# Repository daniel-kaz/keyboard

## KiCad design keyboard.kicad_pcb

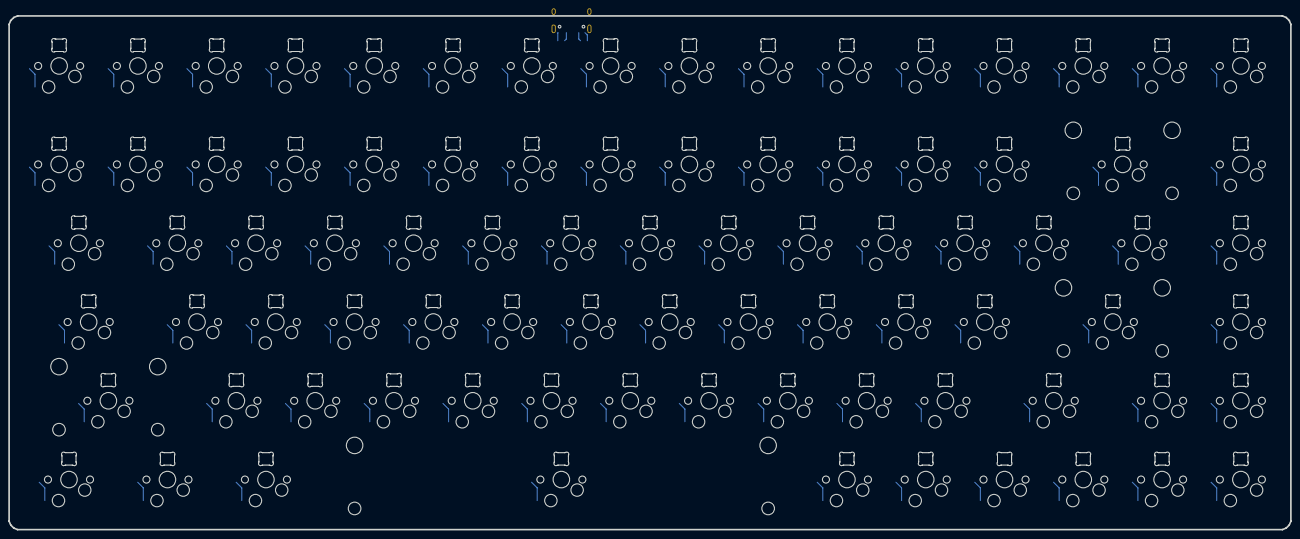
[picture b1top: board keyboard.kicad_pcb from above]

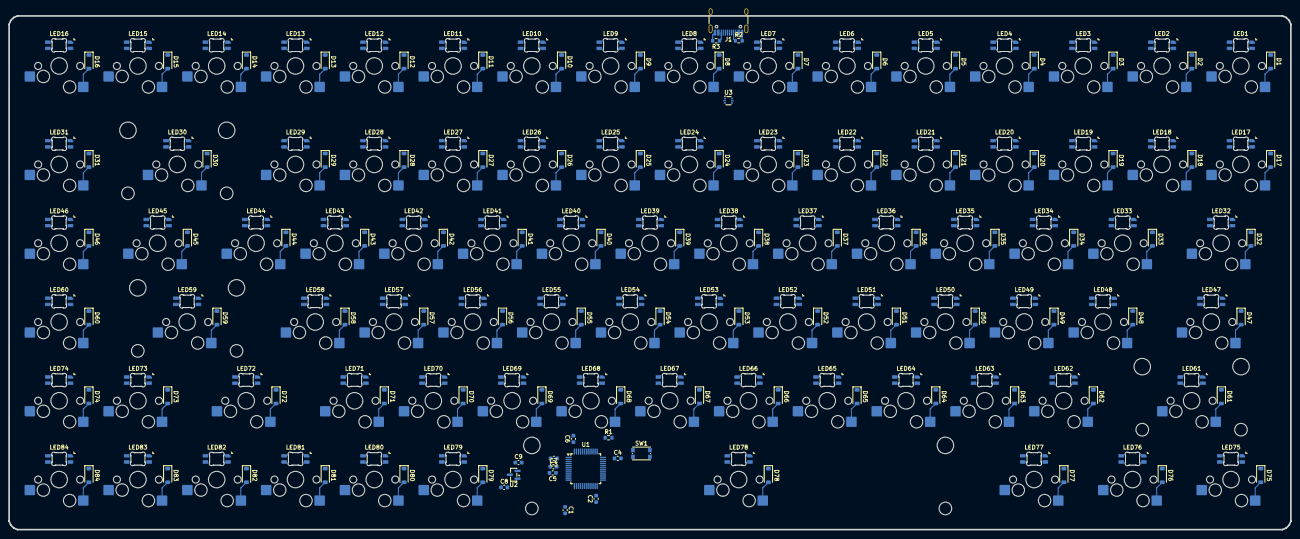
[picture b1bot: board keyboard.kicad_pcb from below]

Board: 2 copper layers, 309.9 x 124.2 mm, 279 parts (269 on the bottom side), 201 nets.

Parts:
C1: 4.7u; C_0603_1608Metric
C2, C3, C4, C5, C7: 100n; C_0603_1608Metric
C6: 10n; C_0603_1608Metric
C8, C9: 1u; C_0603_1608Metric
D1, D2, D3, D4, D5, D6, D7, D8, D9, D10, D11, D12, D13, D14, D15, D16, D17, D18, D19, D20, D21, D22, D23, D24, D25, D26, D27, D28, D29, D30, D31, D32, D33, D34, D35, D36, D37, D38, D39, D40, D41, D42, D43, D44, D45, D46, D47, D48, D49, D50, D51, D52, D53, D54, D55, D56, D57, D58, D59, D60, D61, D62, D63, D64, D65, D66, D67, D68, D69, D70, D71, D72, D73, D74, D75, D76, D77, D78, D79, D80, D81, D82, D83, D84: D; D_SOD-123
H1, H2, H3, H4, H5, H6, H7, H8, H9, H10: MountingHole; MountingHole_2.2mm_M2
J1: USB_C_Receptacle_USB2.0_14P; USB_C_Receptacle_HRO_TYPE-C-31-M-12
LED1, LED2, LED3, LED4, LED5, LED6, LED7, LED8, LED9, LED10, LED11, LED12, LED13, LED14, LED15, LED16, LED17, LED18, LED19, LED20, LED21, LED22, LED23, LED24, LED25, LED26, LED27, LED28, LED29, LED30, LED31, LED32, LED33, LED34, LED35, LED36, LED37, LED38, LED39, LED40, LED41, LED42, LED43, LED44, LED45, LED46, LED47, LED48, LED49, LED50, LED51, LED52, LED53, LED54, LED55, LED56, LED57, LED58, LED59, LED60, LED61, LED62, LED63, LED64, LED65, LED66, LED67, LED68, LED69, LED70, LED71, LED72, LED73, LED74, LED75, LED76, LED77, LED78, LED79, LED80, LED81, LED82, LED83, LED84: SK6812MINI-E; LED_6028R
R1: 10k; R_0603_1608Metric
R2, R3: 5.1k; R_0603_1608Metric
S1: ESC; MX-Hotswap-1U
S2: F1; MX-Hotswap-1U
S3: F2; MX-Hotswap-1U
S4: F3; MX-Hotswap-1U
S5: F4; MX-Hotswap-1U
S6: F5; MX-Hotswap-1U
S7: F6; MX-Hotswap-1U
S8: F7; MX-Hotswap-1U
S9: F8; MX-Hotswap-1U
S10: F9; MX-Hotswap-1U
S11: F10; MX-Hotswap-1U
S12: F11; MX-Hotswap-1U
S13: F12; MX-Hotswap-1U
S14: F13; MX-Hotswap-1U
S15: F14; MX-Hotswap-1U
S16: Magic; MX-Hotswap-1U
S17: GRV; MX-Hotswap-1U
S18: #1; MX-Hotswap-1U
S19: #2; MX-Hotswap-1U
S20: #3; MX-Hotswap-1U
S21: #4; MX-Hotswap-1U
S22: #5; MX-Hotswap-1U
S23: #6; MX-Hotswap-1U
S24: #7; MX-Hotswap-1U
S25: #8; MX-Hotswap-1U
S26: #9; MX-Hotswap-1U
S27: #0; MX-Hotswap-1U
S28: -; MX-Hotswap-1U
S29: =; MX-Hotswap-1U
S30: Backspace; MX-Hotswap-2U
S31: pgup; MX-Hotswap-1U
S32: Tab; MX-Hotswap-1.5U
S33: Q; MX-Hotswap-1U
S34: W; MX-Hotswap-1U
S35: E; MX-Hotswap-1U
S36: R; MX-Hotswap-1U
S37: T; MX-Hotswap-1U
S38: Y; MX-Hotswap-1U
S39: U; MX-Hotswap-1U
S40: I; MX-Hotswap-1U
S41: O; MX-Hotswap-1U
S42: P; MX-Hotswap-1U
S43: {; MX-Hotswap-1U
S44: }; MX-Hotswap-1U
S45: |; MX-Hotswap-1.5U
S46: pgdn; MX-Hotswap-1U
S47: CAPS; MX-Hotswap-1.75U
S48: A; MX-Hotswap-1U
S49: S; MX-Hotswap-1U
S50: D; MX-Hotswap-1U
S51: F; MX-Hotswap-1U
S52: G; MX-Hotswap-1U
S53: H; MX-Hotswap-1U
S54: J; MX-Hotswap-1U
S55: K; MX-Hotswap-1U
S56: L; MX-Hotswap-1U
S57: :; MX-Hotswap-1U
S58: "; MX-Hotswap-1U
S59: Enter; MX-Hotswap-2.25U
S60: Home; MX-Hotswap-1U
S61: LSHIFT; MX-Hotswap-2.25U
S62: Z; MX-Hotswap-1U
S63: X; MX-Hotswap-1U
S64: C; MX-Hotswap-1U
S65: V; MX-Hotswap-1U
S66: B; MX-Hotswap-1U
S67: N; MX-Hotswap-1U
S68: M; MX-Hotswap-1U
S69: <; MX-Hotswap-1U
S70: >; MX-Hotswap-1U
S71: ?; MX-Hotswap-1U
S72: RSHIFT; MX-Hotswap-1.75U
S73: UP; MX-Hotswap-1U
S74: End; MX-Hotswap-1U
S75: LCtrl; MX-Hotswap-1.25U
S76: LWin; MX-Hotswap-1.25U
S77: Alt; MX-Hotswap-1.25U
S78: Space; MX-Hotswap-6.25U
S79: RWin; MX-Hotswap-1U
S80: Fn; MX-Hotswap-1U
S81: RCtrl; MX-Hotswap-1U
S82: LEFT; MX-Hotswap-1U
S83: DOWN; MX-Hotswap-1U
S84: RIGHT; MX-Hotswap-1U
SW1: SW_Push; SW_Push_1P1T_NO_CK_KMR2
U1: STM32F072C8Tx; LQFP-48_7x7mm_P0.5mm
U2: MCP1700x-330xxTT; SOT-23
U3: USBLC6-2P6; SOT-666

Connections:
+3V3: C1.1, C2.1, C3.1, C4.1, C5.1, C6.1, C9.1, SW1.1, U1.1 (VBAT), U1.9 (VDDA), U1.24 (VDD), U1.36 (VDDIO2), U1.48 (VDD), U2.2 (VO)
+5V: C8.1, J1.A4 (VBUS), J1.A9 (VBUS), J1.B4 (VBUS), J1.B9 (VBUS), LED1.1 (VDD), LED2.1 (VDD), LED3.1 (VDD), LED4.1 (VDD), LED5.1 (VDD), LED6.1 (VDD), LED7.1 (VDD), LED8.1 (VDD), LED9.1 (VDD), LED10.1 (VDD), LED11.1 (VDD), LED12.1 (VDD), LED13.1 (VDD), LED14.1 (VDD), LED15.1 (VDD), LED16.1 (VDD), LED17.1 (VDD), LED18.1 (VDD), LED19.1 (VDD), LED20.1 (VDD), LED21.1 (VDD), LED22.1 (VDD), LED23.1 (VDD), LED24.1 (VDD), LED25.1 (VDD), LED26.1 (VDD), LED27.1 (VDD), LED28.1 (VDD), LED29.1 (VDD), LED30.1 (VDD), LED31.1 (VDD), LED32.1 (VDD), LED33.1 (VDD), LED34.1 (VDD), LED35.1 (VDD), LED36.1 (VDD), LED37.1 (VDD), LED38.1 (VDD), LED39.1 (VDD), LED40.1 (VDD), LED41.1 (VDD), LED42.1 (VDD), LED43.1 (VDD), LED44.1 (VDD), LED45.1 (VDD), LED46.1 (VDD), LED47.1 (VDD), LED48.1 (VDD), LED49.1 (VDD), LED50.1 (VDD), LED51.1 (VDD), LED52.1 (VDD), LED53.1 (VDD), LED54.1 (VDD), LED55.1 (VDD), LED56.1 (VDD), LED57.1 (VDD), LED58.1 (VDD), LED59.1 (VDD), LED60.1 (VDD), LED61.1 (VDD), LED62.1 (VDD), LED63.1 (VDD), LED64.1 (VDD), LED65.1 (VDD), LED66.1 (VDD), LED67.1 (VDD), LED68.1 (VDD), LED69.1 (VDD), LED70.1 (VDD), LED71.1 (VDD), LED72.1 (VDD), LED73.1 (VDD), LED74.1 (VDD), LED75.1 (VDD), LED76.1 (VDD), LED77.1 (VDD), LED78.1 (VDD), LED79.1 (VDD), LED80.1 (VDD), LED81.1 (VDD), LED82.1 (VDD), LED83.1 (VDD), LED84.1 (VDD), U2.3 (VI), U3.5 (VBUS)
/ARGB_DIN: LED1.3 (DIN), U1.34 (PA13)
/BOOT0: R1.1, SW1.2, U1.44 (BOOT0)
/MCU_DN: U1.32 (PA11), U3.3 (I/O2)
/MCU_DP: U1.33 (PA12), U3.1 (I/O1)
/USB_DN: J1.A6 (D+), J1.B6 (D+), U3.4 (I/O2)
/USB_DP: J1.A7 (D-), J1.B7 (D-), U3.6 (I/O1)
Col 0: S1.1, S17.1, S32.1, S47.1, S61.1, S75.1, U1.28 (PB15)
Col 1: S2.1, S18.1, S33.1, S48.1, S62.1, S76.1, U1.27 (PB14)
Col 2: S3.1, S19.1, S34.1, S49.1, S63.1, S77.1, U1.26 (PB13)
Col 3: S4.1, S20.1, S35.1, S50.1, S64.1, U1.25 (PB12)
Col 4: S5.1, S21.1, S36.1, S51.1, S65.1, U1.22 (PB11)
Col 5: S6.1, S22.1, S37.1, S52.1, S66.1, S78.1, U1.21 (PB10)
Col 6: S7.1, S23.1, S38.1, S53.1, S67.1, U1.46 (PB9)
Col 7: S8.1, S24.1, S39.1, S54.1, S68.1, U1.45 (PB8)
Col 8: S9.1, S25.1, S40.1, S55.1, S69.1, U1.43 (PB7)
Col 9: S10.1, S26.1, S41.1, S56.1, S70.1, S79.1, U1.42 (PB6)
Col 10: S11.1, S27.1, S42.1, S57.1, S71.1, S80.1, U1.41 (PB5)
Col 11: S12.1, S28.1, S43.1, S58.1, S81.1, U1.40 (PB4)
Col 12: S13.1, S29.1, S44.1, S72.1, S82.1, U1.39 (PB3)
Col 13: S14.1, S30.1, S45.1, S59.1, S73.1, S83.1, U1.20 (PB2)
Col 14: S15.1, S31.1, S46.1, S60.1, S74.1, S84.1, U1.19 (PB1), U1.30 (PA9)
Col 15: S16.1, U1.29 (PA8)
GND: C1.2, C2.2, C3.2, C4.2, C5.2, C6.2, C7.1, C8.2, C9.2, J1.A1 (GND), J1.A12 (GND), J1.B1 (GND), J1.B12 (GND), J1.S1 (SHIELD), LED1.4 (VSS), LED2.4 (VSS), LED3.4 (VSS), LED4.4 (VSS), LED5.4 (VSS), LED6.4 (VSS), LED7.4 (VSS), LED8.4 (VSS), LED9.4 (VSS), LED10.4 (VSS), LED11.4 (VSS), LED12.4 (VSS), LED13.4 (VSS), LED14.4 (VSS), LED15.4 (VSS), LED16.4 (VSS), LED17.4 (VSS), LED18.4 (VSS), LED19.4 (VSS), LED20.4 (VSS), LED21.4 (VSS), LED22.4 (VSS), LED23.4 (VSS), LED24.4 (VSS), LED25.4 (VSS), LED26.4 (VSS), LED27.4 (VSS), LED28.4 (VSS), LED29.4 (VSS), LED30.4 (VSS), LED31.4 (VSS), LED32.4 (VSS), LED33.4 (VSS), LED34.4 (VSS), LED35.4 (VSS), LED36.4 (VSS), LED37.4 (VSS), LED38.4 (VSS), LED39.4 (VSS), LED40.4 (VSS), LED41.4 (VSS), LED42.4 (VSS), LED43.4 (VSS), LED44.4 (VSS), LED45.4 (VSS), LED46.4 (VSS), LED47.4 (VSS), LED48.4 (VSS), LED49.4 (VSS), LED50.4 (VSS), LED51.4 (VSS), LED52.4 (VSS), LED53.4 (VSS), LED54.4 (VSS), LED55.4 (VSS), LED56.4 (VSS), LED57.4 (VSS), LED58.4 (VSS), LED59.4 (VSS), LED60.4 (VSS), LED61.4 (VSS), LED62.4 (VSS), LED63.4 (VSS), LED64.4 (VSS), LED65.4 (VSS), LED66.4 (VSS), LED67.4 (VSS), LED68.4 (VSS), LED69.4 (VSS), LED70.4 (VSS), LED71.4 (VSS), LED72.4 (VSS), LED73.4 (VSS), LED74.4 (VSS), LED75.4 (VSS), LED76.4 (VSS), LED77.4 (VSS), LED78.4 (VSS), LED79.4 (VSS), LED80.4 (VSS), LED81.4 (VSS), LED82.4 (VSS), LED83.4 (VSS), LED84.4 (VSS), R1.2, R2.2, R3.2, U1.8 (VSSA), U1.23 (VSS), U1.35 (VSS), U1.47 (VSS), U2.1 (GND), U3.2 (GND)
unnamed: D1.2 (A), S1.2
unnamed: D2.2 (A), S2.2
unnamed: D3.2 (A), S3.2
unnamed: D4.2 (A), S4.2
unnamed: D5.2 (A), S5.2
unnamed: D6.2 (A), S6.2
unnamed: D7.2 (A), S7.2
unnamed: D8.2 (A), S8.2
unnamed: D9.2 (A), S9.2
unnamed: D10.2 (A), S10.2
unnamed: D11.2 (A), S11.2
unnamed: D12.2 (A), S12.2
unnamed: D13.2 (A), S13.2
unnamed: D14.2 (A), S14.2
unnamed: D15.2 (A), S15.2
unnamed: D16.2 (A), S16.2
unnamed: D17.2 (A), S17.2
unnamed: D18.2 (A), S18.2
unnamed: D19.2 (A), S19.2
unnamed: D20.2 (A), S20.2
unnamed: D21.2 (A), S21.2
unnamed: D22.2 (A), S22.2
unnamed: D23.2 (A), S23.2
unnamed: D24.2 (A), S24.2
unnamed: D25.2 (A), S25.2
unnamed: D26.2 (A), S26.2
unnamed: D27.2 (A), S27.2
unnamed: D28.2 (A), S28.2
unnamed: D29.2 (A), S29.2
unnamed: D30.2 (A), S30.2
unnamed: D31.2 (A), S31.2
unnamed: D32.2 (A), S32.2
unnamed: D33.2 (A), S33.2
unnamed: D34.2 (A), S34.2
unnamed: D35.2 (A), S35.2
unnamed: D36.2 (A), S36.2
unnamed: D37.2 (A), S37.2
unnamed: D38.2 (A), S38.2
unnamed: D39.2 (A), S39.2
unnamed: D40.2 (A), S40.2
unnamed: D41.2 (A), S41.2
unnamed: D42.2 (A), S42.2
unnamed: D43.2 (A), S43.2
unnamed: D44.2 (A), S44.2
unnamed: D45.2 (A), S45.2
unnamed: D46.2 (A), S46.2
unnamed: D47.2 (A), S47.2
unnamed: D48.2 (A), S48.2
unnamed: D49.2 (A), S49.2
unnamed: D50.2 (A), S50.2
unnamed: D51.2 (A), S51.2
unnamed: D52.2 (A), S52.2
unnamed: D53.2 (A), S53.2
unnamed: D54.2 (A), S54.2
unnamed: D55.2 (A), S55.2
unnamed: D56.2 (A), S56.2
unnamed: D57.2 (A), S57.2
unnamed: D58.2 (A), S58.2
unnamed: D59.2 (A), S59.2
unnamed: D60.2 (A), S60.2
unnamed: D61.2 (A), S61.2
unnamed: D62.2 (A), S62.2
unnamed: D63.2 (A), S63.2
unnamed: D64.2 (A), S64.2
unnamed: D65.2 (A), S65.2
unnamed: D66.2 (A), S66.2
unnamed: D67.2 (A), S67.2
unnamed: D68.2 (A), S68.2
unnamed: D69.2 (A), S69.2
unnamed: D70.2 (A), S70.2
unnamed: D71.2 (A), S71.2
unnamed: D72.2 (A), S72.2
unnamed: D73.2 (A), S73.2
unnamed: D74.2 (A), S74.2
unnamed: D75.2 (A), S75.2
unnamed: D76.2 (A), S76.2
unnamed: D77.2 (A), S77.2
unnamed: D78.2 (A), S78.2
unnamed: D79.2 (A), S79.2
unnamed: D80.2 (A), S80.2
unnamed: D81.2 (A), S81.2
unnamed: D82.2 (A), S82.2
unnamed: D83.2 (A), S83.2
unnamed: D84.2 (A), S84.2
unnamed: J1.A5 (CC1), R2.1
unnamed: J1.B5 (CC2), R3.1
unnamed: LED1.2 (DOUT), LED2.3 (DIN)
unnamed: LED2.2 (DOUT), LED3.3 (DIN)
unnamed: LED3.2 (DOUT), LED4.3 (DIN)
unnamed: LED4.2 (DOUT), LED5.3 (DIN)
unnamed: LED5.2 (DOUT), LED6.3 (DIN)
unnamed: LED6.2 (DOUT), LED7.3 (DIN)
unnamed: LED7.2 (DOUT), LED8.3 (DIN)
unnamed: LED8.2 (DOUT), LED9.3 (DIN)
unnamed: LED9.2 (DOUT), LED10.3 (DIN)
unnamed: LED10.2 (DOUT), LED11.3 (DIN)
unnamed: LED11.2 (DOUT), LED12.3 (DIN)
unnamed: LED12.2 (DOUT), LED13.3 (DIN)
unnamed: LED13.2 (DOUT), LED14.3 (DIN)
unnamed: LED14.2 (DOUT), LED15.3 (DIN)
unnamed: LED15.2 (DOUT), LED16.3 (DIN)
unnamed: LED16.2 (DOUT), LED17.3 (DIN)
unnamed: LED17.2 (DOUT), LED18.3 (DIN)
unnamed: LED18.2 (DOUT), LED19.3 (DIN)
unnamed: LED19.2 (DOUT), LED20.3 (DIN)
unnamed: LED20.2 (DOUT), LED21.3 (DIN)
unnamed: LED21.2 (DOUT), LED22.3 (DIN)
unnamed: LED22.2 (DOUT), LED23.3 (DIN)
unnamed: LED23.2 (DOUT), LED24.3 (DIN)
unnamed: LED24.2 (DOUT), LED25.3 (DIN)
unnamed: LED25.2 (DOUT), LED27.3 (DIN)
unnamed: LED26.3 (DIN), LED47.2 (DOUT)
unnamed: LED26.2 (DOUT), LED28.3 (DIN)
unnamed: LED27.2 (DOUT), LED29.3 (DIN)
unnamed: LED28.2 (DOUT), LED30.3 (DIN)
unnamed: LED29.2 (DOUT), LED31.3 (DIN)
unnamed: LED30.2 (DOUT), LED32.3 (DIN)
unnamed: LED31.2 (DOUT), LED33.3 (DIN)
unnamed: LED32.2 (DOUT), LED34.3 (DIN)
unnamed: LED33.2 (DOUT), LED35.3 (DIN)
unnamed: LED34.2 (DOUT), LED36.3 (DIN)
unnamed: LED35.2 (DOUT), LED37.3 (DIN)
unnamed: LED36.2 (DOUT), LED38.3 (DIN)
unnamed: LED37.2 (DOUT), LED39.3 (DIN)
unnamed: LED38.2 (DOUT), LED40.3 (DIN)
unnamed: LED39.2 (DOUT), LED41.3 (DIN)
unnamed: LED40.2 (DOUT), LED42.3 (DIN)
unnamed: LED41.2 (DOUT), LED43.3 (DIN)
unnamed: LED42.2 (DOUT), LED44.3 (DIN)
unnamed: LED43.2 (DOUT), LED45.3 (DIN)
unnamed: LED44.2 (DOUT), LED46.3 (DIN)
unnamed: LED45.2 (DOUT), LED47.3 (DIN)
unnamed: LED46.2 (DOUT), LED48.3 (DIN)
unnamed: LED48.2 (DOUT), LED49.3 (DIN)
unnamed: LED49.2 (DOUT), LED52.3 (DIN)
unnamed: LED50.3 (DIN), LED82.2 (DOUT)
unnamed: LED50.2 (DOUT), LED53.3 (DIN)
unnamed: LED51.3 (DIN), LED83.2 (DOUT)
unnamed: LED51.2 (DOUT), LED54.3 (DIN)
unnamed: LED52.2 (DOUT), LED55.3 (DIN)
unnamed: LED53.2 (DOUT), LED56.3 (DIN)
unnamed: LED54.2 (DOUT), LED57.3 (DIN)
unnamed: LED55.2 (DOUT), LED58.3 (DIN)
unnamed: LED56.2 (DOUT), LED59.3 (DIN)
unnamed: LED57.2 (DOUT), LED60.3 (DIN)
unnamed: LED58.2 (DOUT), LED61.3 (DIN)
unnamed: LED59.2 (DOUT), LED62.3 (DIN)
unnamed: LED60.2 (DOUT), LED63.3 (DIN)
unnamed: LED61.2 (DOUT), LED64.3 (DIN)
unnamed: LED62.2 (DOUT), LED65.3 (DIN)
unnamed: LED63.2 (DOUT), LED66.3 (DIN)
unnamed: LED64.2 (DOUT), LED67.3 (DIN)
unnamed: LED65.2 (DOUT), LED68.3 (DIN)
unnamed: LED66.2 (DOUT), LED69.3 (DIN)
unnamed: LED67.2 (DOUT), LED70.3 (DIN)
unnamed: LED68.2 (DOUT), LED71.3 (DIN)
unnamed: LED69.2 (DOUT), LED72.3 (DIN)
unnamed: LED70.2 (DOUT), LED73.3 (DIN)
unnamed: LED71.2 (DOUT), LED74.3 (DIN)
unnamed: LED72.2 (DOUT), LED75.3 (DIN)
unnamed: LED73.2 (DOUT), LED76.3 (DIN)
unnamed: LED74.2 (DOUT), LED77.3 (DIN)
unnamed: LED75.2 (DOUT), LED78.3 (DIN)
unnamed: LED76.2 (DOUT), LED79.3 (DIN)
unnamed: LED77.2 (DOUT), LED80.3 (DIN)
unnamed: LED78.2 (DOUT), LED81.3 (DIN)
unnamed: LED79.2 (DOUT), LED82.3 (DIN)
unnamed: LED80.2 (DOUT), LED83.3 (DIN)
unnamed: LED81.2 (DOUT), LED84.3 (DIN)
unnamed: C7.2, U1.7 (NRST)
Row 0: D1.1 (K), D2.1 (K), D3.1 (K), D4.1 (K), D5.1 (K), D6.1 (K), D7.1 (K), D8.1 (K), D9.1 (K), D10.1 (K), D11.1 (K), D12.1 (K), D13.1 (K), D14.1 (K), D15.1 (K), D16.1 (K), U1.13 (PA3)
Row 1: D17.1 (K), D18.1 (K), D19.1 (K), D20.1 (K), D21.1 (K), D22.1 (K), D23.1 (K), D24.1 (K), D25.1 (K), D26.1 (K), D27.1 (K), D28.1 (K), D29.1 (K), D30.1 (K), D31.1 (K), U1.14 (PA4)
Row 2: D32.1 (K), D33.1 (K), D34.1 (K), D35.1 (K), D36.1 (K), D37.1 (K), D38.1 (K), D39.1 (K), D40.1 (K), D41.1 (K), D42.1 (K), D43.1 (K), D44.1 (K), D45.1 (K), D46.1 (K), U1.15 (PA5)
Row 3: D47.1 (K), D48.1 (K), D49.1 (K), D50.1 (K), D51.1 (K), D52.1 (K), D53.1 (K), D54.1 (K), D55.1 (K), D56.1 (K), D57.1 (K), D58.1 (K), D59.1 (K), D60.1 (K), U1.16 (PA6)
Row 4: D61.1 (K), D62.1 (K), D63.1 (K), D64.1 (K), D65.1 (K), D66.1 (K), D67.1 (K), D68.1 (K), D69.1 (K), D70.1 (K), D71.1 (K), D72.1 (K), D73.1 (K), D74.1 (K), U1.17 (PA7)
Row 5: D75.1 (K), D76.1 (K), D77.1 (K), D78.1 (K), D79.1 (K), D80.1 (K), D81.1 (K), D82.1 (K), D83.1 (K), D84.1 (K), U1.18 (PB0)

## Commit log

2025-10-30 init commit with schematic
2026-01-22 pico breakout version
2026-02-21 placed components on pcb
2026-02-21 small fixes to schematic
2026-03-01 first full version of pcb complete
2026-03-08 various footprint fixes
2026-03-08 working on plate
2026-03-09 added keyboard plate
2026-03-10 made every cut extrusion needed
2026-03-11 pcb ready for review
2026-03-11 plate ready for review
2026-03-12 pcb review changes
2026-03-12 production ready
